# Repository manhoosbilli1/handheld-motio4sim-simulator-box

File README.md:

# handheld1_motion4sim_FO41AFC70E184

Handheld controller for Motio4sim driving simulator

## At a Glance

- **Status**: Routed
- **Board size**: (unknown)
- **Layers**: 2
- **Components**: ?

## Renders

**PCB top**

**PCB bottom**

## Files

- `handheld1_motion4sim_FO41AFC70E184.kicad_pro` - KiCad project
- `handheld1_motion4sim_FO41AFC70E184.kicad_sch` - schematic source
- `handheld1_motion4sim_FO41AFC70E184.kicad_pcb` - PCB layout source
- `reports/schematic.pdf` - full schematic (printable)
- `reports/bom.csv` - bill of materials
- `reports/pcb-top.svg`, `reports/pcb-bottom.svg` - copper artwork
- `reports/board-stats.json` - KiCad-generated board statistics

## Notes

Title block: 'Handheld1 Device'. Existing GH repo is empty - simple push.

---

_Renders and metadata auto-generated by `Backup-KiCadProject.ps1` using KiCad 10.0._

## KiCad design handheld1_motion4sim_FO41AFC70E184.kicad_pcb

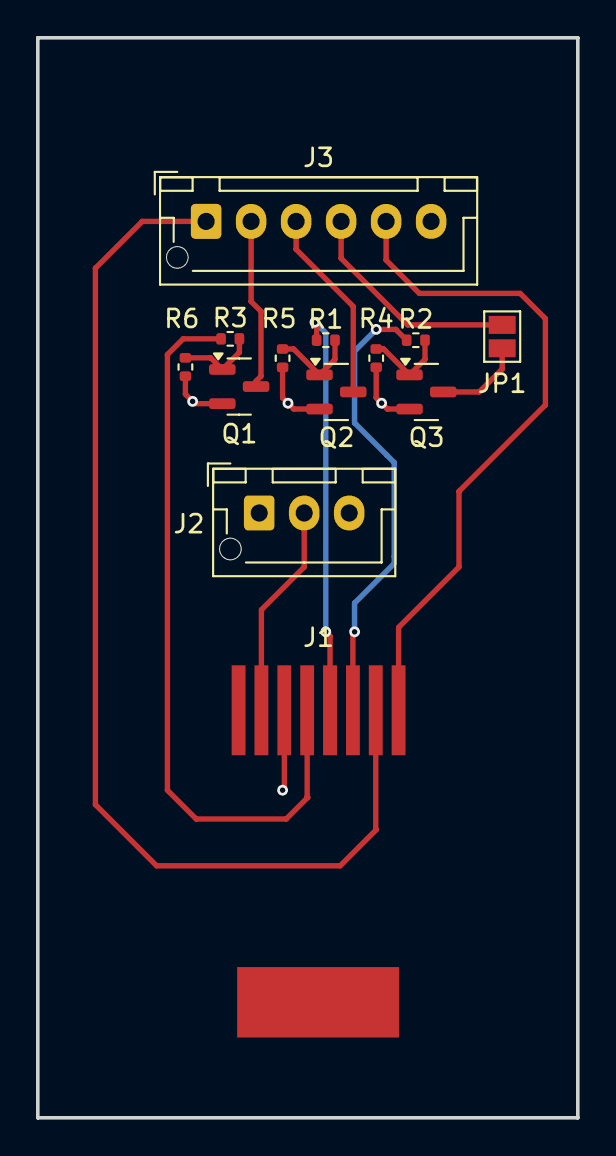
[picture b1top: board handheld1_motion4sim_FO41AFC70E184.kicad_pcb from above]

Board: 2 copper layers, 30.0 x 60.0 mm, 13 parts (0 on the bottom side), 14 nets.

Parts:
J1: RJ45; RJ45_Molex_0855135013_Vertical
J2: Conn_01x03; JST_XH_B3B-XH-AM_1x03_P2.50mm_Vertical
J3: Conn_01x06; JST_XH_B6B-XH-AM_1x06_P2.50mm_Vertical
JP1: Jumper_2_Open; SolderJumper-2_P1.3mm_Open_Pad1.0x1.5mm
Q1, Q2, Q3: AO3400A; SOT-23
R1, R2, R3: 100; R_0402_1005Metric
R4, R5, R6: 100k; R_0402_1005Metric

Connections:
/G_cathode: J3.3, Q2.3 (D)
/R_cathode: J3.2, Q1.3 (D)
/Y_cathode: J3.4, JP1.2 (B)
FAULTSTOP: J1.2, J2.2
GND: J1.3, J2.1, J3.6, Q1.2 (S), Q2.2 (S), Q3.2 (S), R4.1, R5.1, R6.1
LED_GREEN: J1.5, R1.1
LED_RED: J1.4, R3.1
LED_YELLOW: J1.6, R2.1
unnamed: JP1.1 (A), Q3.3 (D)
unnamed: Q1.1 (G), R3.2, R6.2
unnamed: Q2.1 (G), R1.2, R5.2
unnamed: Q3.1 (G), R2.2, R4.2
ONLINE: J1.7, J3.1
VCC_5V0: J1.8, J3.5

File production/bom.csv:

Designator,Footprint,Quantity,Value,LCSC Part #
J1,RJ45_Molex_0855135013_Vertical,1,RJ45,C708653
J2,JST_XH_B3B-XH-AM_1x03_P2.50mm_Vertical,1,Conn_01x03,C161870
J3,JST_XH_B6B-XH-AM_1x06_P2.50mm_Vertical,1,Conn_01x06,C161873
JP1,SolderJumper-2_P1.3mm_Open_Pad1.0x1.5mm,1,Jumper_2_Open,
"Q1, Q2, Q3",SOT-23,3,AO3400A,C20917
"R1, R2, R3",0402,3,100,C25076
"R4, R5, R6",0402,3,100k,C25530

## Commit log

2025-10-01 started the project schematic almost complete
2025-10-01 change gitignore
2025-10-01 added gitignore
2025-10-19 shoaib
2025-10-19 completed
2026-05-18 Add backup artifacts: 3D renders, BOM, board stats, generated README
2026-05-18 Enrich README: schematic PNG, component roles, BOM table
